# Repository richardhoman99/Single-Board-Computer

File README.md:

# Single Board Computer

CPGR4253 Microcomputer Design is not as much a technical course at LeTourneau University as it is a design project. The goal of the course is to design a functioning Single Board Computer with the following requirements:
- A microprocessor
- At least 64Kib RAM
- ROM memory to store monitor program
- Serial connection to external terminal

This repository is the container of all digital files supporting this project.

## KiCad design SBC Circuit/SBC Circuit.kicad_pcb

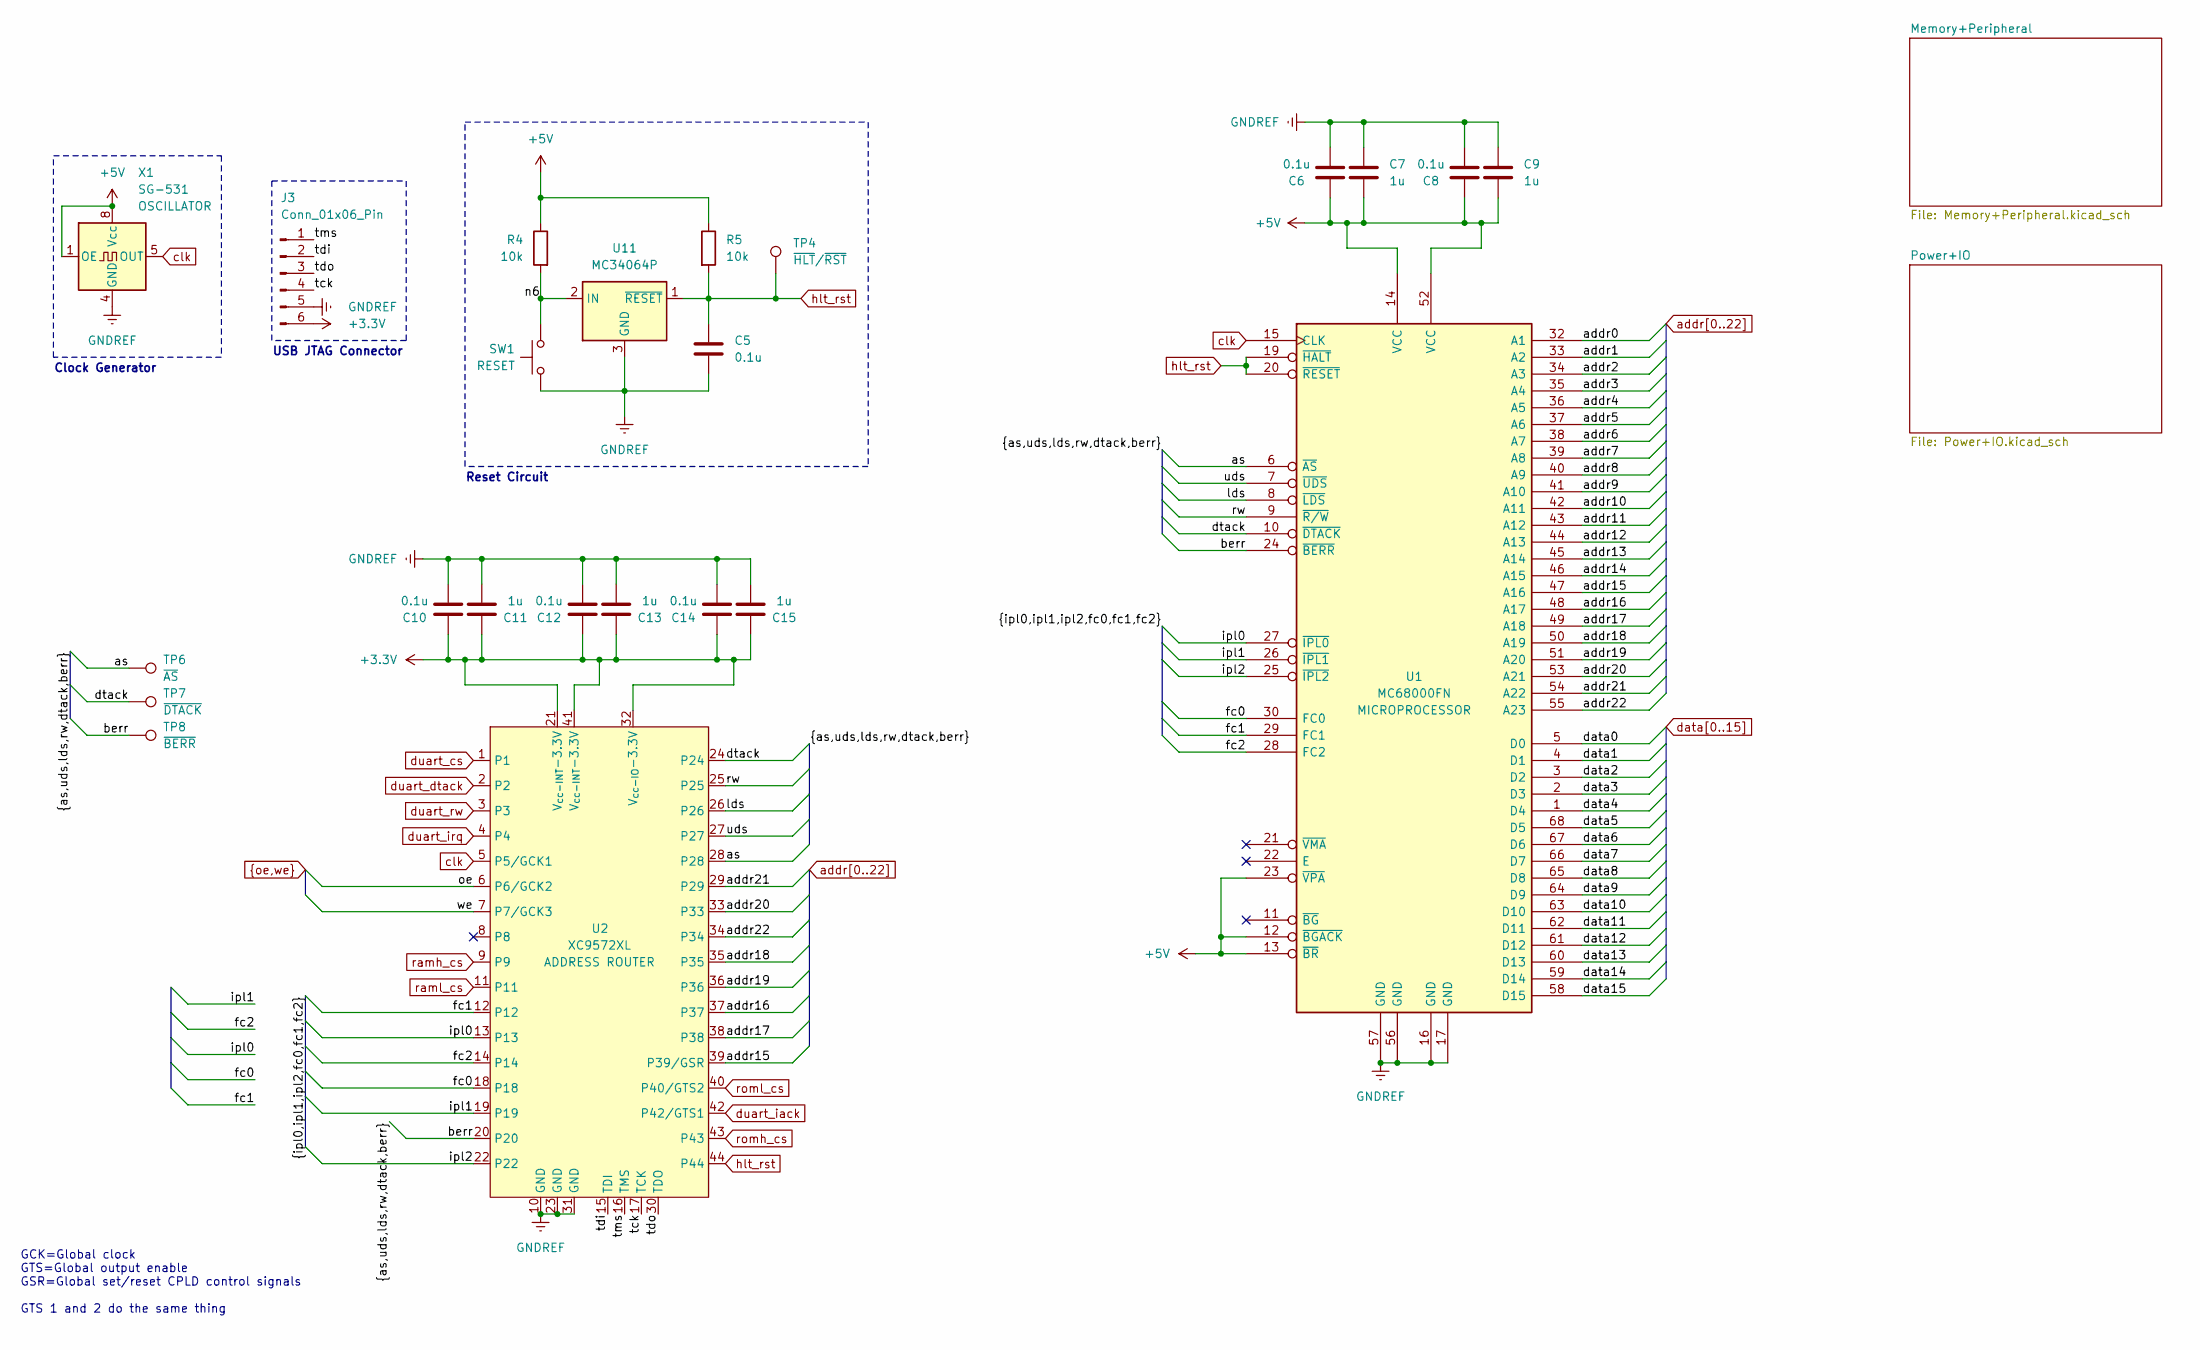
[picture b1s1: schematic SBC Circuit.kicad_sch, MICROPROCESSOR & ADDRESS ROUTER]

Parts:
C5, C6, C8, C10, C12, C14: 0.1u; CP_Disc_L5.50mm_W4.00mm_P2.50mm_NonPolarized
C7, C9, C11, C13, C15: 1u; CP_Disc_L5.50mm_W4.00mm_P2.50mm_NonPolarized
J3: Conn_01x06_Pin; PinHeader_1x06_P2.54mm_Vertical
R4, R5: 10k; R_Axial_DIN0204_L3.6mm_D1.6mm_P2.54mm_Vertical
SW1: RESET; SW_PUSH_6mm
TP4: ~{HLT}/~{RST}; TestPoint_Keystone_5000-5004_Miniature
TP6: ~{AS}; TestPoint_Keystone_5000-5004_Miniature
TP7: ~{DTACK}; TestPoint_Keystone_5000-5004_Miniature
TP8: ~{BERR}; TestPoint_Keystone_5000-5004_Miniature
U1: MC68000FN; PLCC-68_THT-Socket
U2: XC9572XL; PLCC-44_THT-Socket
U11: MC34064P; TO-92_Inline
X1: SG-531; Oscillator_SeikoEpson_SG-8002DC

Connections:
+3.3V: C10.1, C11.1, C12.1, C13.1, C14.1, C15.1, J3.6, U2.21 (V_{cc-INT}-3.3V), U2.32 (V_{cc-IO}-3.3V), U2.41 (V_{cc-INT}-3.3V); also elsewhere on the board
+5V: C6.1, C7.1, C8.1, C9.1, R4.1, R5.1, U1.12 (~BGACK), U1.13 (~BR), U1.14 (VCC), U1.23 (~VPA), U1.52 (VCC), X1.1 (OE), X1.8 (Vcc); also elsewhere on the board
/as: TP6.1, U1.6 (~AS), U2.28
/berr: TP8.1, U1.24 (~BERR), U2.20
/dtack: TP7.1, U1.10 (~DTACK), U2.24
/fc0: U1.30 (FC0), U2.18
/fc1: U1.29 (FC1), U2.12
/fc2: U1.28 (FC2), U2.14
/ipl0: U1.27 (~IPL0), U2.13
/ipl1: U1.26 (~IPL1), U2.19
/ipl2: U1.25 (~IPL2), U2.22
/lds: U1.8 (~LDS), U2.26
/n6: R4.2, SW1.1, U11.2 (IN)
/rw: U1.9 (~R/W), U2.25
/tck: J3.4, U2.17 (TCK)
/tdi: J3.2, U2.15 (TDI)
/tdo: J3.3, U2.30 (TDO)
/tms: J3.1, U2.16 (TMS)
/uds: U1.7 (~UDS), U2.27
GNDREF: C5.2, C6.2, C7.2, C8.2, C9.2, C10.2, C11.2, C12.2, C13.2, C14.2, C15.2, J3.5, SW1.2, U1.16 (GND), U1.17 (GND), U1.56 (GND), U1.57 (GND), U2.10 (GND), U2.23 (GND), U2.31 (GND), U11.3 (GND), X1.4 (GND); also elsewhere on the board
addr0: U1.32 (A1); also elsewhere on the board
addr1: U1.33 (A2); also elsewhere on the board
addr2: U1.34 (A3); also elsewhere on the board
addr3: U1.35 (A4); also elsewhere on the board
addr4: U1.36 (A5); also elsewhere on the board
addr5: U1.37 (A6); also elsewhere on the board
addr6: U1.38 (A7); also elsewhere on the board
addr7: U1.39 (A8); also elsewhere on the board
addr8: U1.40 (A9); also elsewhere on the board
addr9: U1.41 (A10); also elsewhere on the board
addr10: U1.42 (A11); also elsewhere on the board
addr11: U1.43 (A12); also elsewhere on the board
addr12: U1.44 (A13); also elsewhere on the board
addr13: U1.45 (A14); also elsewhere on the board
addr14: U1.46 (A15); also elsewhere on the board
addr15: U1.47 (A16), U2.39 (P39/GSR)
addr16: U1.48 (A17), U2.37
addr17: U1.49 (A18), U2.38
addr18: U1.50 (A19), U2.35
addr19: U1.51 (A20), U2.36
addr20: U1.53 (A21), U2.33
addr21: U1.54 (A22), U2.29
addr22: U1.55 (A23), U2.34
clk: U1.15 (CLK), U2.5 (P5/GCK1), X1.5 (OUT)
data0: U1.5 (D0); also elsewhere on the board
data1: U1.4 (D1); also elsewhere on the board
data2: U1.3 (D2); also elsewhere on the board
data3: U1.2 (D3); also elsewhere on the board
data4: U1.1 (D4); also elsewhere on the board
data5: U1.68 (D5); also elsewhere on the board
data6: U1.67 (D6); also elsewhere on the board
data7: U1.66 (D7); also elsewhere on the board
data8: U1.65 (D8); also elsewhere on the board
data9: U1.64 (D9); also elsewhere on the board
data10: U1.63 (D10); also elsewhere on the board
data11: U1.62 (D11); also elsewhere on the board
data12: U1.61 (D12); also elsewhere on the board
data13: U1.60 (D13); also elsewhere on the board
data14: U1.59 (D14); also elsewhere on the board
data15: U1.58 (D15); also elsewhere on the board
duart_cs: U2.1; also elsewhere on the board
duart_dtack: U2.2; also elsewhere on the board
duart_iack: U2.42 (P42/GTS1); also elsewhere on the board
duart_irq: U2.4; also elsewhere on the board
duart_rw: U2.3; also elsewhere on the board
hlt_rst: C5.1, R5.2, TP4.1, U1.19 (~HALT), U1.20 (~RESET), U2.44, U11.1 (~RESET); also elsewhere on the board
oe: U2.6 (P6/GCK2); also elsewhere on the board
ramh_cs: U2.9; also elsewhere on the board
raml_cs: U2.11; also elsewhere on the board
romh_cs: U2.43; also elsewhere on the board
roml_cs: U2.40 (P40/GTS2); also elsewhere on the board
we: U2.7 (P7/GCK3); also elsewhere on the board

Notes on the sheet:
Reset Circuit
USB JTAG Connector
GCK=Global clock GTS=Global output enable GSR=Global set/reset CPLD control signals GTS 1 and 2 do the same thing
Clock Generator

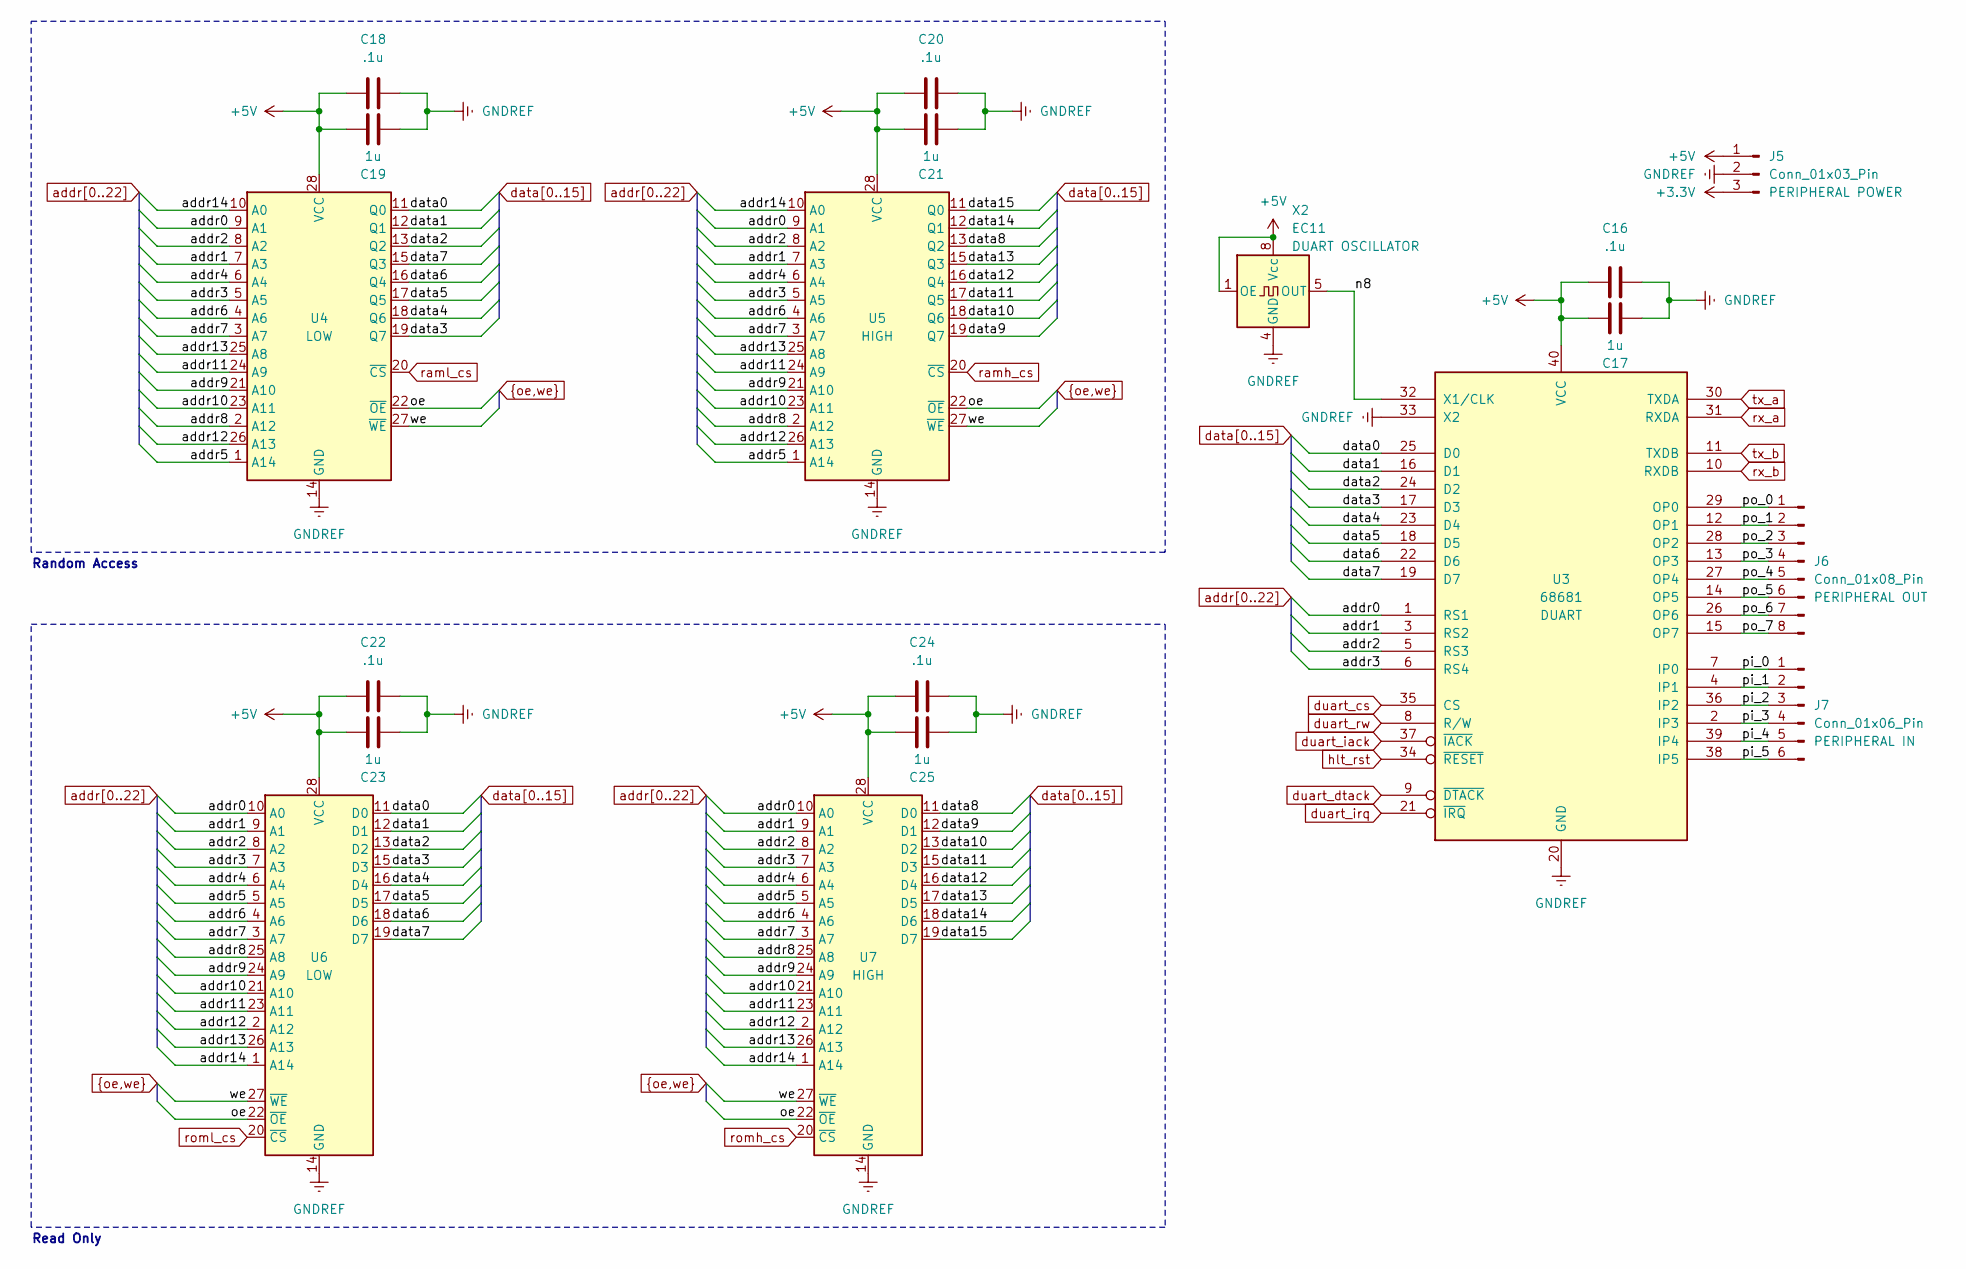
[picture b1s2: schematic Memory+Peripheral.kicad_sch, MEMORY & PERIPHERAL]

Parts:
C16, C18, C20, C22, C24: .1u; CP_Disc_L5.50mm_W4.00mm_P2.50mm_NonPolarized
C17, C19, C21, C23, C25: 1u; CP_Disc_L5.50mm_W4.00mm_P2.50mm_NonPolarized
J5: Conn_01x03_Pin; PinHeader_1x03_P2.54mm_Vertical
J6: Conn_01x08_Pin; PinHeader_1x08_P2.54mm_Vertical
J7: Conn_01x06_Pin; PinHeader_1x06_P2.54mm_Vertical
U3: 68681; DIP-40_W15.24mm_Socket
U4, U5: MCM6206CP; DIP-28_W7.62mm_Socket
U6, U7: 28C256; DIP-28_W15.24mm_Socket
X2: EC11; Oscillator_DIP-8

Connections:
+3.3V: J5.3; also elsewhere on the board
+5V: C16.1, C17.1, C18.1, C19.1, C20.1, C21.1, C22.1, C23.1, C24.1, C25.1, J5.1, U3.40 (VCC), U4.28 (VCC), U5.28 (VCC), U6.28 (VCC), U7.28 (VCC), X2.1 (OE), X2.8 (Vcc); also elsewhere on the board
/Memory+Peripheral/n8: U3.32 (X1/CLK), X2.5 (OUT)
/Memory+Peripheral/pi_0: J7.1, U3.7 (IP0)
/Memory+Peripheral/pi_1: J7.2, U3.4 (IP1)
/Memory+Peripheral/pi_2: J7.3, U3.36 (IP2)
/Memory+Peripheral/pi_3: J7.4, U3.2 (IP3)
/Memory+Peripheral/pi_4: J7.5, U3.39 (IP4)
/Memory+Peripheral/pi_5: J7.6, U3.38 (IP5)
/Memory+Peripheral/po_0: J6.1, U3.29 (OP0)
/Memory+Peripheral/po_1: J6.2, U3.12 (OP1)
/Memory+Peripheral/po_2: J6.3, U3.28 (OP2)
/Memory+Peripheral/po_3: J6.4, U3.13 (OP3)
/Memory+Peripheral/po_4: J6.5, U3.27 (OP4)
/Memory+Peripheral/po_5: J6.6, U3.14 (OP5)
/Memory+Peripheral/po_6: J6.7, U3.26 (OP6)
/Memory+Peripheral/po_7: J6.8, U3.15 (OP7)
GNDREF: C16.2, C17.2, C18.2, C19.2, C20.2, C21.2, C22.2, C23.2, C24.2, C25.2, J5.2, U3.20 (GND), U3.33 (X2), U4.14 (GND), U5.14 (GND), U6.14 (GND), U7.14 (GND), X2.4 (GND); also elsewhere on the board
addr0: U3.1 (RS1), U4.9 (A1), U5.9 (A1), U6.10 (A0), U7.10 (A0); also elsewhere on the board
addr1: U3.3 (RS2), U4.7 (A3), U5.7 (A3), U6.9 (A1), U7.9 (A1); also elsewhere on the board
addr2: U3.5 (RS3), U4.8 (A2), U5.8 (A2), U6.8 (A2), U7.8 (A2); also elsewhere on the board
addr3: U3.6 (RS4), U4.5 (A5), U5.5 (A5), U6.7 (A3), U7.7 (A3); also elsewhere on the board
addr4: U4.6 (A4), U5.6 (A4), U6.6 (A4), U7.6 (A4); also elsewhere on the board
addr5: U4.1 (A14), U5.1 (A14), U6.5 (A5), U7.5 (A5); also elsewhere on the board
addr6: U4.4 (A6), U5.4 (A6), U6.4 (A6), U7.4 (A6); also elsewhere on the board
addr7: U4.3 (A7), U5.3 (A7), U6.3 (A7), U7.3 (A7); also elsewhere on the board
addr8: U4.2 (A12), U5.2 (A12), U6.25 (A8), U7.25 (A8); also elsewhere on the board
addr9: U4.21 (A10), U5.21 (A10), U6.24 (A9), U7.24 (A9); also elsewhere on the board
addr10: U4.23 (A11), U5.23 (A11), U6.21 (A10), U7.21 (A10); also elsewhere on the board
addr11: U4.24 (A9), U5.24 (A9), U6.23 (A11), U7.23 (A11); also elsewhere on the board
addr12: U4.26 (A13), U5.26 (A13), U6.2 (A12), U7.2 (A12); also elsewhere on the board
addr13: U4.25 (A8), U5.25 (A8), U6.26 (A13), U7.26 (A13); also elsewhere on the board
addr14: U4.10 (A0), U5.10 (A0), U6.1 (A14), U7.1 (A14); also elsewhere on the board
data0: U3.25 (D0), U4.11 (Q0), U6.11 (D0); also elsewhere on the board
data1: U3.16 (D1), U4.12 (Q1), U6.12 (D1); also elsewhere on the board
data2: U3.24 (D2), U4.13 (Q2), U6.13 (D2); also elsewhere on the board
data3: U3.17 (D3), U4.19 (Q7), U6.15 (D3); also elsewhere on the board
data4: U3.23 (D4), U4.18 (Q6), U6.16 (D4); also elsewhere on the board
data5: U3.18 (D5), U4.17 (Q5), U6.17 (D5); also elsewhere on the board
data6: U3.22 (D6), U4.16 (Q4), U6.18 (D6); also elsewhere on the board
data7: U3.19 (D7), U4.15 (Q3), U6.19 (D7); also elsewhere on the board
data8: U5.13 (Q2), U7.11 (D0); also elsewhere on the board
data9: U5.19 (Q7), U7.12 (D1); also elsewhere on the board
data10: U5.18 (Q6), U7.13 (D2); also elsewhere on the board
data11: U5.17 (Q5), U7.15 (D3); also elsewhere on the board
data12: U5.16 (Q4), U7.16 (D4); also elsewhere on the board
data13: U5.15 (Q3), U7.17 (D5); also elsewhere on the board
data14: U5.12 (Q1), U7.18 (D6); also elsewhere on the board
data15: U5.11 (Q0), U7.19 (D7); also elsewhere on the board
duart_cs: U3.35 (CS); also elsewhere on the board
duart_dtack: U3.9 (~DTACK); also elsewhere on the board
duart_iack: U3.37 (~IACK); also elsewhere on the board
duart_irq: U3.21 (~IRQ); also elsewhere on the board
duart_rw: U3.8 (R/W); also elsewhere on the board
hlt_rst: U3.34 (~RESET); also elsewhere on the board
oe: U4.22 (~OE), U5.22 (~OE), U6.22 (~OE), U7.22 (~OE); also elsewhere on the board
ramh_cs: U5.20 (~CS); also elsewhere on the board
raml_cs: U4.20 (~CS); also elsewhere on the board
romh_cs: U7.20 (~CS); also elsewhere on the board
roml_cs: U6.20 (~CS); also elsewhere on the board
rx_a: U3.31 (RXDA); also elsewhere on the board
rx_b: U3.10 (RXDB); also elsewhere on the board
tx_a: U3.30 (TXDA); also elsewhere on the board
tx_b: U3.11 (TXDB); also elsewhere on the board
we: U4.27 (~WE), U5.27 (~WE), U6.27 (~WE), U7.27 (~WE); also elsewhere on the board

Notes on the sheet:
Read Only
Random Access

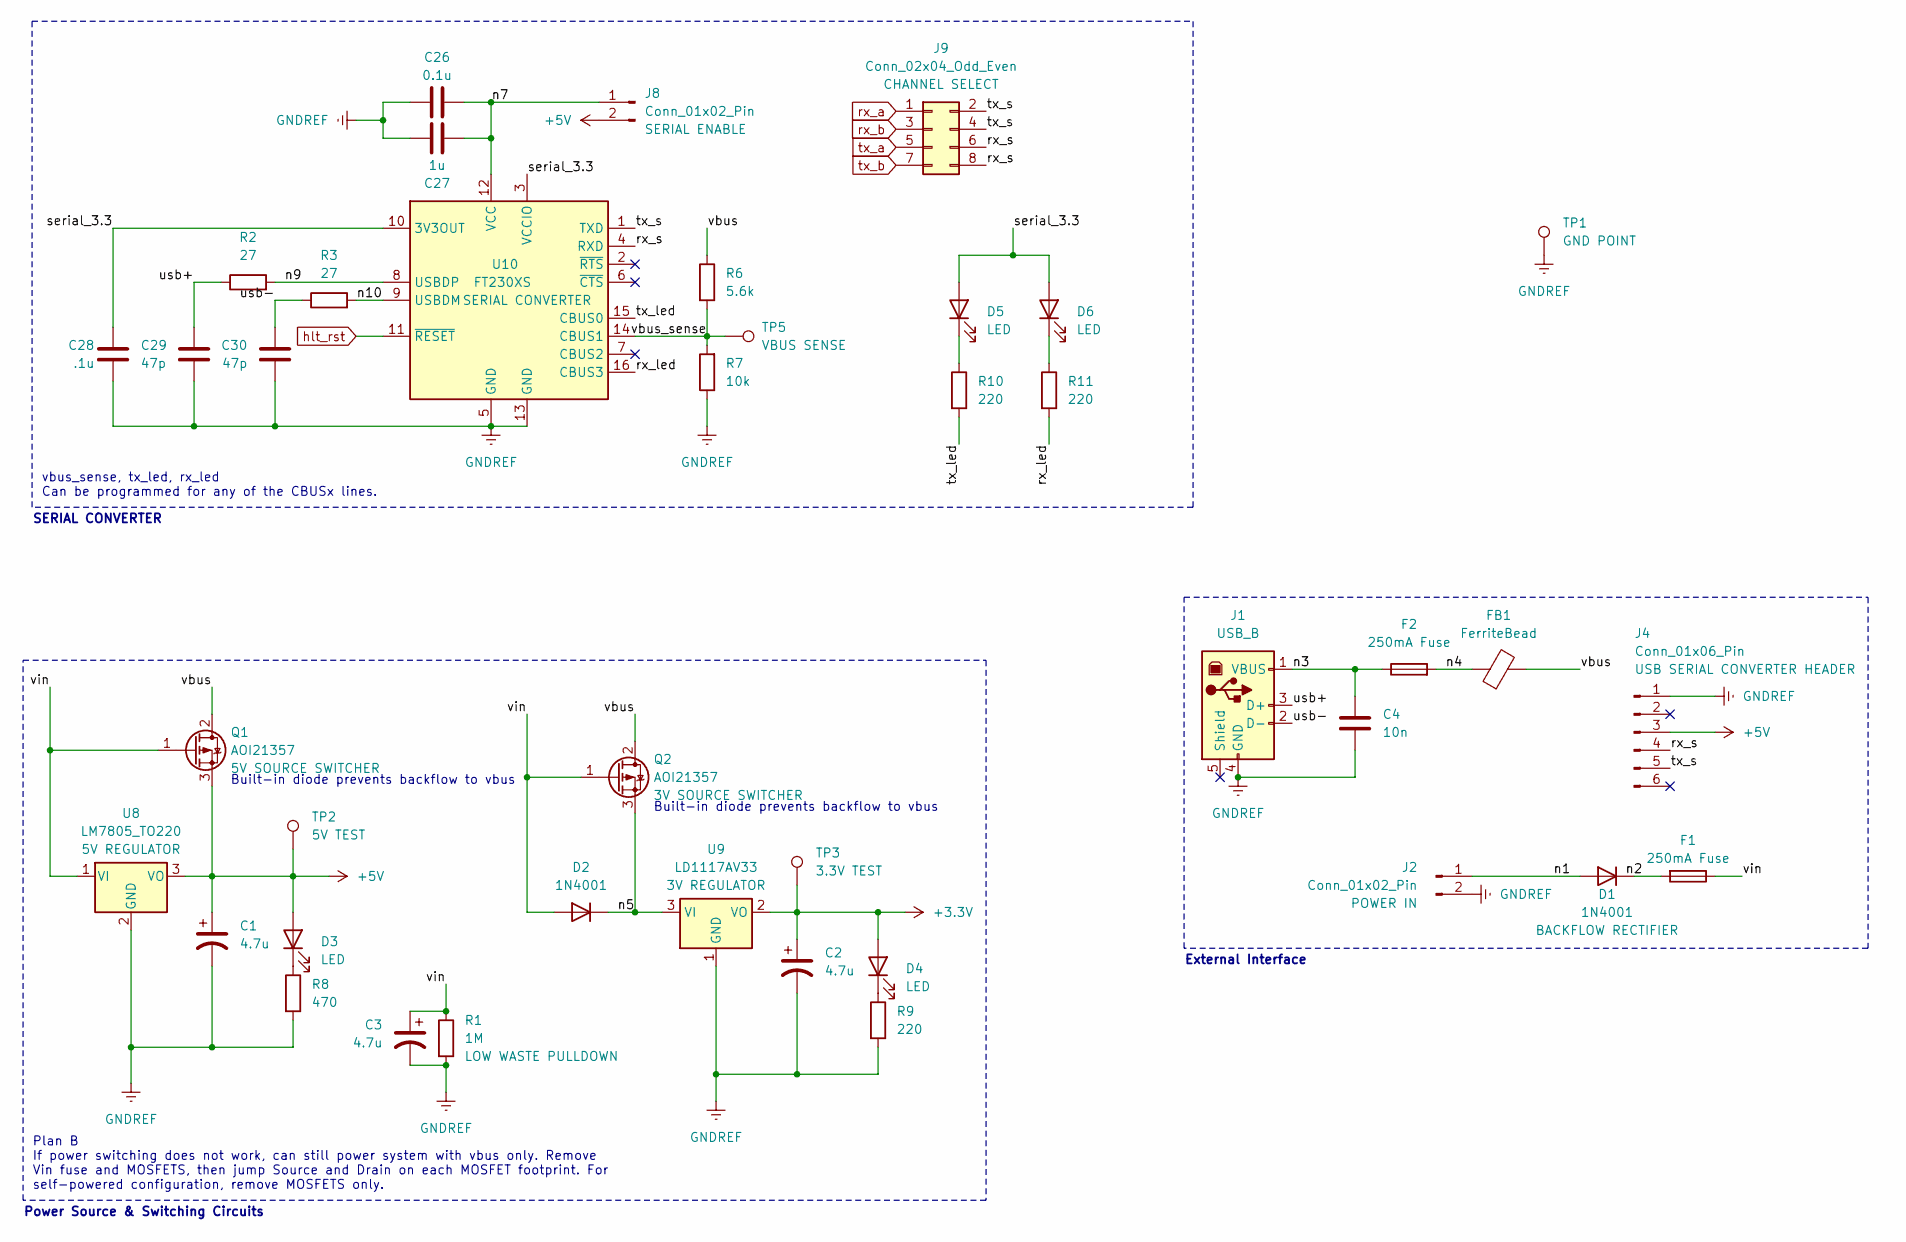
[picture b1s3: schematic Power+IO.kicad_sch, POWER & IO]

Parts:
C1, C2, C3: 4.7u; CP_Radial_D4.0mm_P2.00mm
C4: 10n; CP_Disc_L5.50mm_W4.00mm_P2.50mm_NonPolarized
C26: 0.1u; CP_Disc_L5.50mm_W4.00mm_P2.50mm_NonPolarized
C27: 1u; CP_Disc_L5.50mm_W4.00mm_P2.50mm_NonPolarized
C28: .1u; CP_Disc_L5.50mm_W4.00mm_P2.50mm_NonPolarized
C29, C30: 47p; CP_Disc_L5.50mm_W4.00mm_P2.50mm_NonPolarized
D1, D2: 1N4001; D_DO-41_SOD81_P5.08mm_Vertical_KathodeUp
D3, D4, D5, D6: LED; LED_D5.0mm
F1, F2: 250mA Fuse; Fuseholder_Clip-5x20mm_Bel_FC-203-22_Lateral_P17.80x5.00mm_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
FB1: FerriteBead; C_Axial_L3.8mm_D2.6mm_P10.00mm_Horizontal
J1: USB_B; USB_B_OST_USB-B1HSxx_Horizontal
J2, J8: Conn_01x02_Pin; PinHeader_1x02_P2.54mm_Vertical
J4: Conn_01x06_Pin; PinHeader_1x06_P2.54mm_Vertical
J9: Conn_02x04_Odd_Even; PinHeader_2x04_P2.54mm_Vertical
Q1, Q2: AOI21357; TO-220-3_Vertical
R1: 1M; R_Axial_DIN0204_L3.6mm_D1.6mm_P2.54mm_Vertical
R2, R3: 27; R_Axial_DIN0204_L3.6mm_D1.6mm_P2.54mm_Vertical
R6: 5.6k; R_Axial_DIN0204_L3.6mm_D1.6mm_P2.54mm_Vertical
R7: 10k; R_Axial_DIN0204_L3.6mm_D1.6mm_P2.54mm_Vertical
R8: 470; R_Axial_DIN0204_L3.6mm_D1.6mm_P2.54mm_Vertical
R9, R10, R11: 220; R_Axial_DIN0204_L3.6mm_D1.6mm_P2.54mm_Vertical
TP1: GND POINT; TestPoint_Keystone_5000-5004_Miniature
TP2: 5V TEST; TestPoint_Keystone_5000-5004_Miniature
TP3: 3.3V TEST; TestPoint_Keystone_5000-5004_Miniature
TP5: VBUS SENSE; TestPoint_Keystone_5000-5004_Miniature
U8: LM7805_TO220; TO-220-3_Vertical
U9: LD1117AV33; TO-220-3_Vertical
U10: FT230XS; SSOP-16_3.9x4.9mm_P0.635mm

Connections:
+3.3V: C2.1, D4.2 (A), TP3.1, U9.2 (VO); also elsewhere on the board
+5V: C1.1, D3.2 (A), J4.3, J8.2, Q1.3 (S), TP2.1, U8.3 (VO); also elsewhere on the board
/Power+IO/n1: D1.2 (A), J2.1
/Power+IO/n2: D1.1 (K), F1.2
/Power+IO/n3: C4.1, F2.1, J1.1 (VBUS)
/Power+IO/n4: F2.2, FB1.1
/Power+IO/n5: D2.1 (K), Q2.3 (S), U9.3 (VI)
/Power+IO/n7: C26.1, C27.1, J8.1, U10.12 (VCC)
/Power+IO/n9: R2.2, U10.8 (USBDP)
/Power+IO/n10: R3.2, U10.9 (USBDM)
/Power+IO/rx_led: R11.2, U10.16 (CBUS3)
/Power+IO/rx_s: J4.4, J9.6, J9.8, U10.4 (RXD)
/Power+IO/serial_3.3: C28.1, D5.2 (A), D6.2 (A), U10.3 (VCCIO), U10.10 (3V3OUT)
/Power+IO/tx_led: R10.2, U10.15 (CBUS0)
/Power+IO/tx_s: J4.5, J9.2, J9.4, U10.1 (TXD)
/Power+IO/usb+: C29.1, J1.3 (D+), R2.1
/Power+IO/usb-: C30.1, J1.2 (D-), R3.1
/Power+IO/vbus: FB1.2, Q1.2 (D), Q2.2 (D), R6.1
/Power+IO/vbus_sense: R6.2, R7.2, TP5.1, U10.14 (CBUS1)
/Power+IO/vin: C3.1, D2.2 (A), F1.1, Q1.1 (G), Q2.1 (G), R1.1, U8.1 (VI)
GNDREF: C1.2, C2.2, C3.2, C4.2, C26.2, C27.2, C28.2, C29.2, C30.2, J1.4 (GND), J2.2, J4.1, R1.2, R7.1, R8.2, R9.2, TP1.1, U8.2 (GND), U9.1 (GND), U10.5 (GND), U10.13 (GND); also elsewhere on the board
unnamed: D3.1 (K), R8.1
unnamed: D4.1 (K), R9.1
unnamed: D5.1 (K), R10.1
unnamed: D6.1 (K), R11.1
hlt_rst: U10.11 (~RESET); also elsewhere on the board
rx_a: J9.1; also elsewhere on the board
rx_b: J9.3; also elsewhere on the board
tx_a: J9.5; also elsewhere on the board
tx_b: J9.7; also elsewhere on the board

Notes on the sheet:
vbus_sense, tx_led, rx_led Can be programmed for any of the CBUSx lines.
Built-in diode prevents backflow to vbus
External Interface
SERIAL CONVERTER
Plan B If power switching does not work, can still power system with vbus only. Remove Vin fuse and MOSFETS, then jump Source and Drain on each MOSFET footprint. For self-powered configuration, remove MOSFETS only.
Power Source & Switching Circuits

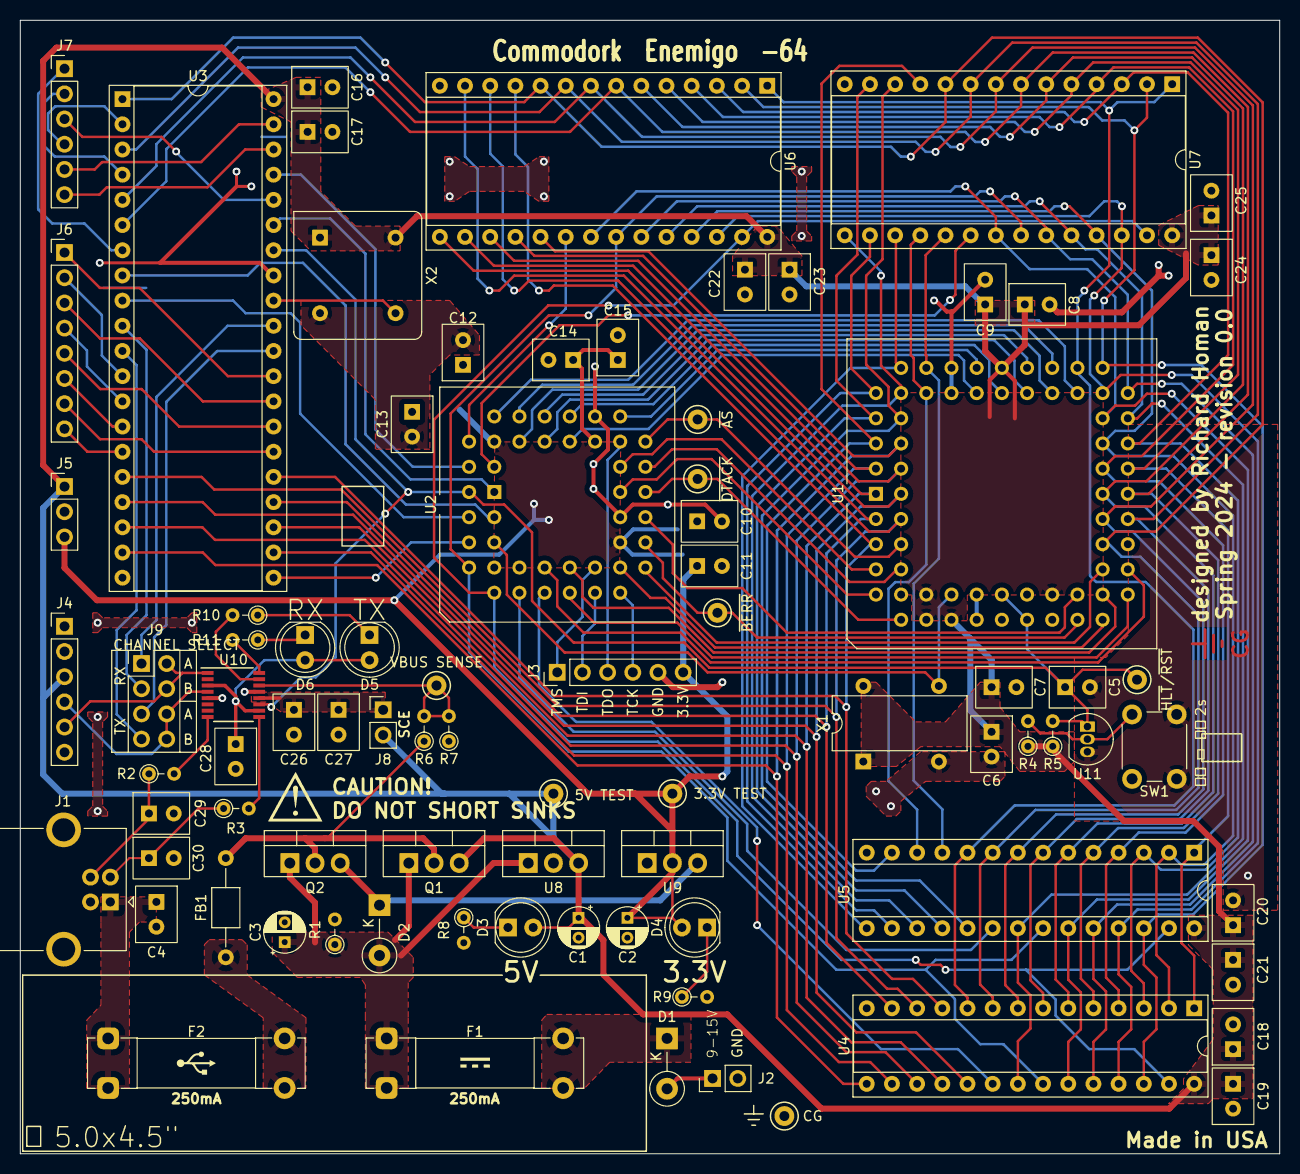
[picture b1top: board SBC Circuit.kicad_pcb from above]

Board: 2 copper layers, 127.0 x 114.3 mm, 83 parts (0 on the bottom side), 113 nets.

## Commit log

2024-01-14 Initial commit
    Add resources
    Add .gitignore
2024-01-14 Populate readme
2024-01-15 Initial KiCad commit
    Wired up RAM and ROM
    Modified Parts List
2024-01-15 Design Schematic
    Rev 0 progress: 70%
2024-01-18 Updates to Schematic
2024-01-18 Small changes to prepare for review
2024-01-22 New part selections, serial port selection
2024-01-22 Update schematic version
2024-01-22 Finish Week Report 2
2024-01-22 Create footprints
2024-01-22 Add peripheral headers to schematic
2024-01-22 Reannotate schematic
2024-01-22 Assign Footprints
2024-01-22 Grouped footprints on PCB
2024-01-23 Fix intersheet bus issues
2024-01-24 PCB CPLD to MPU lines wired
2024-01-24 Wire reset circuit
2024-01-24 Wire fuses and USB jack
2024-01-25 Wire Serial
2024-01-25 Set Serial circuit into place
2024-01-25 Finish power and IO circuit
2024-01-26 Begin final PCB placement
2024-01-26 Begin wiring DUART
2024-01-26 Complete DUART lines
2024-01-27 Finish DUART lines
2024-01-27 Update revision notes and time sheet
2024-01-27 ROM high connected
2024-01-27 Commit before design change
2024-01-28 Wire ROM low
2024-01-28 Finished wiring ROM High
2024-01-29 Wire high ROM correctly
2024-01-29 Add graphic
2024-01-31 Create 11x17
2024-01-31 Commit before design change 2
2024-02-02 Wire phase done
2024-02-02 Connect some power lines
2024-02-04 All lines connected
2024-02-04 Add ground test point
2024-02-04 Update font, add zones to fuses
2024-02-04 Update date
2024-02-05 Created weekly report 4
2024-02-06 Make final adjustments before export
2024-02-06 More refinements
2024-02-06 Export fab outputs for different countries
2024-02-07 Update schematic and PCB for requested changes
2024-02-09 Finalize PCB, neaten up Schematic
2024-02-11 Begin monitor development
2024-02-13 Program basic memory and register actions
2024-02-13 Create first iteration srec loader
2024-02-16 Begin srec parser error reporting
2024-02-18 Finish lsrec loader
2024-02-18 Working srec loader and runner
2024-02-18 Convert to hashmap based command determination
2024-02-19 Neaten monitor code
2024-02-26 Add weekly report 7
2024-03-03 Update time sheet
2024-03-06 Update .gitignore
    Remove autogenerated files which a windows machine generated when cloning the repo
2024-03-08 Create Address Router VHD project
2024-03-18 Add muliplexer to AddressDecoder
2024-03-20 Update time and create weekly reports
2024-03-20 ISE files
2024-03-20 Write bench test
2024-03-22 Finish AddressRouter VHDL
2024-03-22 Create directory for Weekly Reports
2024-03-22 Add AddressRouter program verification feature
2024-03-22 Refactor serial-sim to serial
2024-03-24 Create RAM/ROM test program
2024-03-25 Debug AddressRouter logic
2024-03-25 Update timesheet
2024-03-25 Debug AddressRouter
2024-03-28 Update rr-test, timesheet
2024-03-29 Update rr-test
2024-03-29 Create drt-test
2024-04-02 Update AddressRouter
2024-04-02 Finish DUART test program
2024-04-03 Update Hello, World and EMS programs for 24-bit
2024-04-05 Finalize monitor program
2024-04-05 Fix backspace issue
2024-04-09 Begin mini 2048 game development
2024-04-09 Combine moves into one function
2024-04-09 Finish game
2024-04-10 Finish final presentation
2024-04-12 Update welcome for demo executable
2024-04-17 Finish final presentation, begin final report
2024-04-17 Finish final report
